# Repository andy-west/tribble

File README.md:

# tribble
Code and other resources for making a tribble toy that vibrates and makes sound

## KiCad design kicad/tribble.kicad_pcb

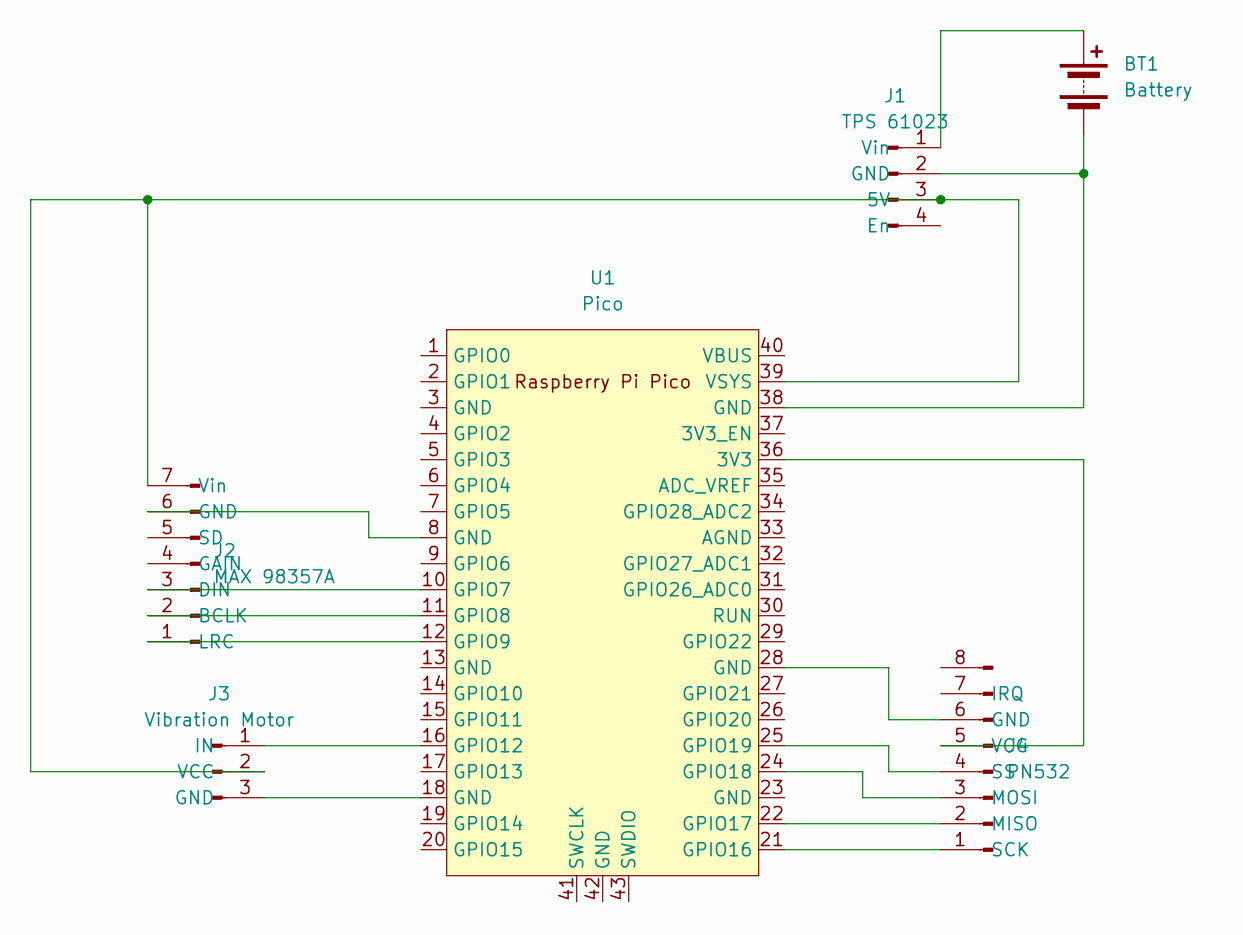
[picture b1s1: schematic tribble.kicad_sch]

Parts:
BT1: Battery; PinHeader_1x02_P2.54mm_Vertical
J1: TPS 61023; PinHeader_1x04_P2.54mm_Vertical
J2: MAX 98357A; PinHeader_1x07_P2.54mm_Vertical
J3: Vibration Motor; PinHeader_1x03_P2.54mm_Vertical
J4: PN532; PinHeader_1x08_P2.54mm_Vertical
U1: Pico; RPi_Pico_SMD_TH

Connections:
unnamed: BT1.1 (+), J1.1 (Vin)
unnamed: BT1.2 (-), J1.2 (GND), U1.38 (GND)
unnamed: J1.3 (5V), J2.7 (Vin), J3.2 (VCC), U1.39 (VSYS)
unnamed: J2.2 (BCLK), U1.11 (GPIO8)
unnamed: J2.3 (DIN), U1.10 (GPIO7)
unnamed: J2.6 (GND), U1.8 (GND)
unnamed: J2.1 (LRC), U1.12 (GPIO9)
unnamed: J3.3 (GND), U1.18 (GND)
unnamed: J3.1 (IN), U1.16 (GPIO12)
unnamed: J4.6 (GND), U1.28 (GND)
unnamed: J4.2 (MISO), U1.22 (GPIO17)
unnamed: J4.3 (MOSI), U1.24 (GPIO18)
unnamed: J4.1 (SCK), U1.21 (GPIO16)
unnamed: J4.4 (SS), U1.25 (GPIO19)
unnamed: J4.5 (VCC), U1.36 (3V3)

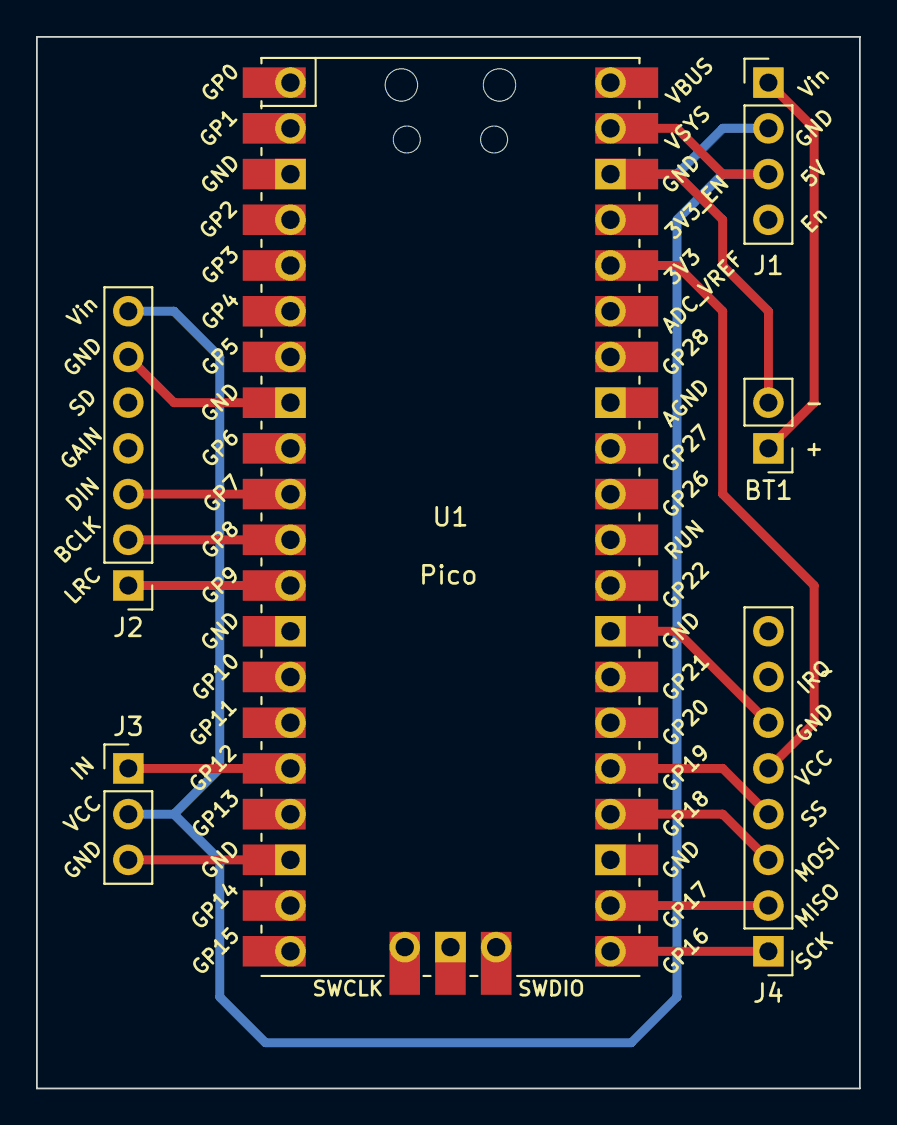
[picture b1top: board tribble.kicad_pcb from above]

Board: 2 copper layers, 45.7 x 58.4 mm, 6 parts (0 on the bottom side), 15 nets.

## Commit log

2024-01-29 Added initial files.
